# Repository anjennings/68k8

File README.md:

# 68k8

## Specs
+ 68008 CPU
+ 68681 UART
+ 32K EEPROM
+ 2 x 512k SRAM Sockets 
	+ 2nd chip (lower) optional
+ Serial EEPROM 
	+ Remotely Programable
	+ Sizes Vary but 64k-128k Recommended
+ Micro SD Card
	+ I haven't even begun to test this so idk

## TODO List 1/7/21 (preferably in this order)
+ Arduino code for programming SROM
+ Wait for new 68681 chips to arrive
+ Finish UART A drivers
+ Finish Timer drivers
+ Test/Finish SROM Drivers
+ Order higher capacity SROM
+ Order sd card slot
+ Order 32-DIP socket for 2nd RAM slot
+ Write bootloader that boots from SROM
+ Solder SD card
+ Solder 2nd RAM socket
+ Assign traps to UART/SPI functions
+ Fuzix Branch

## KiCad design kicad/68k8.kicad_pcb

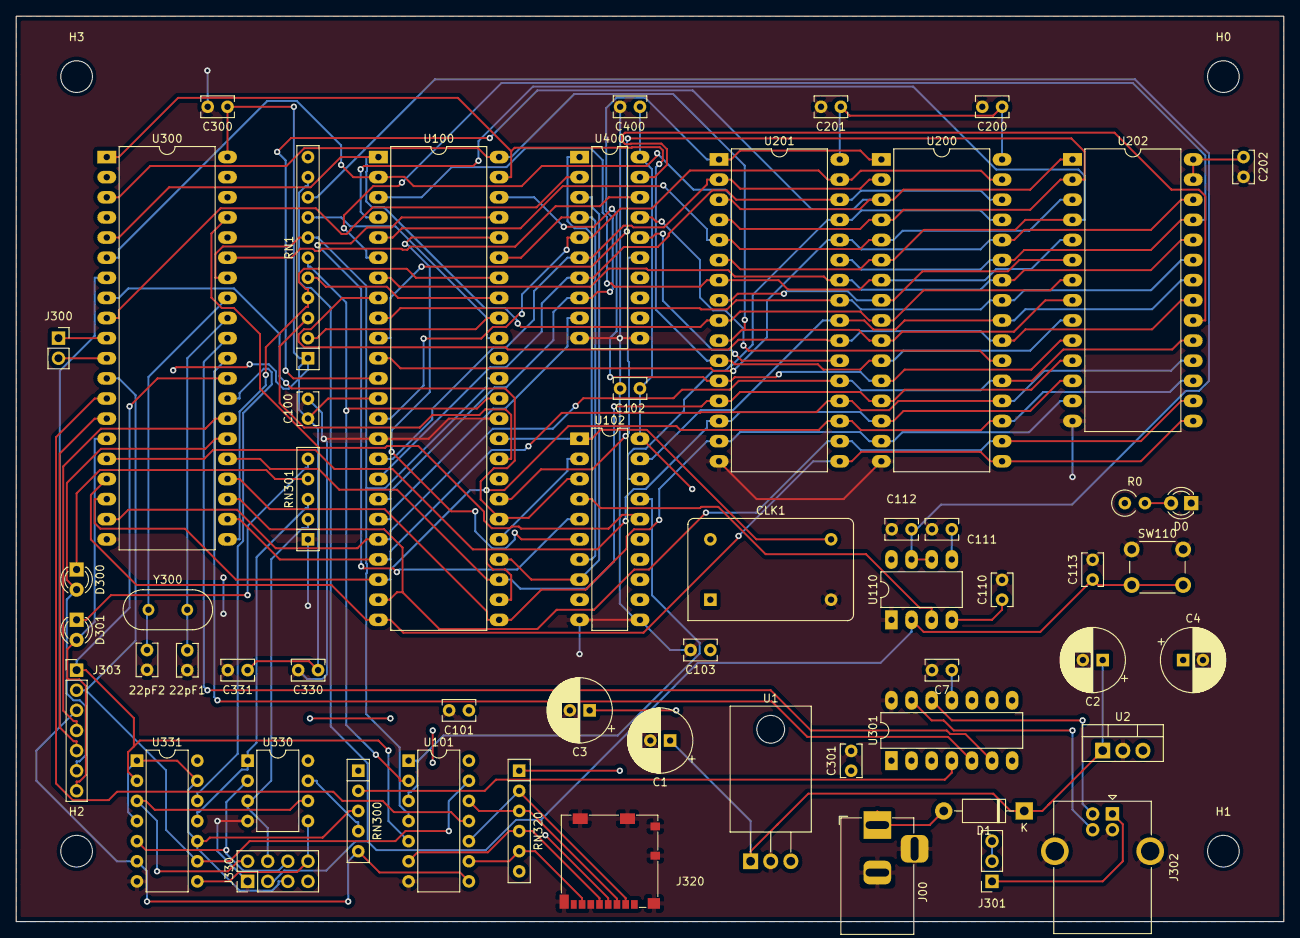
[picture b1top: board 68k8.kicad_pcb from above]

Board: 2 copper layers, 160.0 x 114.3 mm, 60 parts (0 on the bottom side), 96 nets.

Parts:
22pF1: CX1; C_Rect_L4.0mm_W2.5mm_P2.50mm
22pF2: CX2; C_Rect_L4.0mm_W2.5mm_P2.50mm
C1, C4: .1uF; CP_Radial_D8.0mm_P2.50mm
C2: .33uF; CP_Radial_D8.0mm_P2.50mm
C3: 2.2uF; CP_Radial_D8.0mm_P2.50mm
C7, C100, C101, C102, C103, C110, C200, C201, C202, C300, C301, C330, C331, C400: 22pF; C_Rect_L4.0mm_W2.5mm_P2.50mm
C111: 10nF; C_Rect_L4.0mm_W2.5mm_P2.50mm
C112: 10uF; C_Rect_L4.0mm_W2.5mm_P2.50mm
C113: 100nF; C_Rect_L4.0mm_W2.5mm_P2.50mm
CLK1: 10.000 MHz; Oscillator_DIP-14
D0: POW_LED; LED_D3.0mm
D1: 1N4001; D_DO-41_SOD81_P10.16mm_Horizontal
D300, D301: LED; LED_D3.0mm
H0, H1, H2, H3: MountingHole; MountingHole_4mm
J00: Barrel_Jack_Switch; BarrelJack_Horizontal
J300: Conn_01x02_Male; PinSocket_1x02_P2.54mm_Vertical
J301: Conn_01x03_Male; PinSocket_1x03_P2.54mm_Vertical
J302: USB_B; USB_B_OST_USB-B1HSxx_Horizontal
J303: Conn_01x07; PinHeader_1x07_P2.54mm_Vertical
J320: Micro_SD_Card_Det; microSD_HC_Molex_104031-0811
J330: Conn_02x04_Top_Bottom; PinHeader_2x04_P2.54mm_Vertical
R0: 2K; R_Axial_DIN0309_L9.0mm_D3.2mm_P2.54mm_Vertical
RN1: R_Network10; R_Array_SIP11
RN300: 10K; R_Array_SIP5
RN301: 2K; R_Array_SIP5
RN320: 10k; R_Array_SIP6
SW110: SW_Push; SW_PUSH_6mm_H8.5mm
U1: LF33_TO220; TO-220-3_Horizontal_TabDown
U2: L7805; TO-220-3_Vertical
U100: 68008D; DIP-48_W15.24mm_LongPads
U101: 74LS07; DIP-14_W7.62mm
U102, U400: GAL16V8; DIP-20_W7.62mm_LongPads
U110: LM555; DIP-8_W7.62mm_LongPads
U200, U201: AS6C4008-55PCN; DIP-32_W15.24mm_LongPads
U202: 28C256; DIP-28_W15.24mm_LongPads
U300: 68681; DIP-40_W15.24mm_LongPads
U301: MCP2221AxP; DIP-14_W7.62mm_LongPads
U330: 25LCxxx; DIP-8_W7.62mm
U331: 74LS126; DIP-14_W7.62mm
Y300: 3.6864 MHz; Crystal_HC18-U_Vertical

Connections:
555_01: C112.1, RN1.9, U110.6, U110.7
+3V3: C3.1, J320.4, RN320.1, U1.3
+5V: C4.1, C100.1, C101.1, C102.1, C103.1, C110.1, C200.1, C201.1, C202.1, C300.1, C301.1, C330.1, C331.1, C400.1, CLK1.14, J330.7, R0.1, RN1.1, RN300.1, U2.3, U100.13, U101.14, U102.20, U110.4, U110.8, U200.32, U201.32, U202.27, U202.28, U300.40, U301.1, U330.8, U331.14, U400.20
/100_CPU/110_RESET/Reset: U102.4, U110.3
/100_CPU/A0: U100.46, U200.12, U201.12, U202.10
/100_CPU/A1: U100.47, U200.11, U201.11, U202.9, U300.1
/100_CPU/A2: U100.48, U200.10, U201.10, U202.8, U300.3
/100_CPU/A3: U100.1, U200.9, U201.9, U202.7, U300.5
/100_CPU/A4: U100.2, U200.8, U201.8, U202.6, U300.6
/100_CPU/A5: U100.3, U200.7, U201.7, U202.5
/100_CPU/A6: U100.4, U200.6, U201.6, U202.4
/100_CPU/A7: U100.5, U200.5, U201.5, U202.3
/100_CPU/A8: U100.6, U200.27, U201.27, U202.25
/100_CPU/A9: U100.7, U200.26, U201.26, U202.24
/100_CPU/A10: U100.8, U200.23, U201.23, U202.21
/100_CPU/A11: U100.9, U200.25, U201.25, U202.23
/100_CPU/A12: U100.10, U200.4, U201.4, U202.2
/100_CPU/A13: U100.11, U200.28, U201.28, U202.26
/100_CPU/A14: U100.12, U200.3, U201.3, U202.1
/100_CPU/A15: U100.14, U200.31, U201.31, U400.5
/100_CPU/A16: U100.16, U200.2, U201.2, U400.6
/100_CPU/A17: U100.17, U200.30, U201.30, U400.7
/100_CPU/A18: U100.18, U200.1, U201.1, U400.8
/100_CPU/A19: U100.19, U400.9
/100_CPU/D0: U100.27, U200.13, U201.13, U202.11, U300.25
/100_CPU/D1: U100.26, U200.14, U201.14, U202.12, U300.16
/100_CPU/D2: U100.25, U200.15, U201.15, U202.13, U300.24
/100_CPU/D3: U100.24, U200.17, U201.17, U202.15, U300.17
/100_CPU/D4: U100.23, U200.18, U201.18, U202.16, U300.23
/100_CPU/D5: U100.22, U200.19, U201.19, U202.17, U300.18
/100_CPU/D6: U100.21, U200.20, U201.20, U202.18, U300.22
/100_CPU/D7: U100.20, U200.21, U201.21, U202.19, U300.19
AS: U100.28, U102.8, U400.3
AUX_CS1: J303.4, U300.27
AUX_CS2: J303.5, U300.14
AUX_CS3: D300.2, J303.6, U300.26
AUX_CS4: D301.2, J303.7, U300.15
BERR: RN1.2, U100.40
BR: RN1.3, U100.33
CLK: CLK1.8, U100.34, U102.1, U400.1
DART_DTACK: U300.9, U400.2
DART_IRQ: RN1.4, U100.42, U300.21
DART_RX: U300.31, U301.6
DART_TX: U300.30, U301.5
DS: U100.29, U102.2
DTACK: U100.31, U400.15
FC0: U100.45, U102.5
FC1: U100.44, U102.6
FC2: U100.43, U102.7, U400.4
GND: 22pF1.1, 22pF2.1, C1.2, C2.2, C3.2, C4.2, C7.2, C100.2, C101.2, C102.2, C103.2, C110.2, C111.2, C112.2, C113.2, C200.2, C201.2, C202.2, C300.2, C301.2, C330.2, C331.2, C400.2, CLK1.7, D0.1, J00.2, J00.3, J302.4, J302.5, J320.6, J320.9, J320.10, J320.11, J330.1, RN301.1, SW110.1, U1.2, U2.2, U100.15, U100.35, U101.7, U102.10, U102.11, U110.1, U200.16, U201.16, U202.14, U300.20, U301.14, U330.4, U331.7, U400.10, U400.11
HALT: RN1.6, U100.36, U101.2
HRAM_SEL: U200.22, U400.17
INTACK: U102.16, U300.37
IO1_SEL: U300.35, U400.18
IP1: RN1.5, U100.41
LRAM_SEL: U201.22, U400.16
MISO: J303.3, RN300.5, U101.8, U300.7, U331.6
MOSI: J303.2, U101.13, U300.12, U331.9
unnamed: 22pF1.2, U300.32, Y300.1
unnamed: 22pF2.2, U300.33, Y300.2
unnamed: C7.1, U301.11
unnamed: C111.1, U110.5
unnamed: D0.2, R0.2
unnamed: D1.2, J00.1
unnamed: D300.1, RN301.4
unnamed: D301.1, RN301.5
unnamed: J300.1, U300.10
unnamed: J300.2, U300.11
unnamed: J301.1, J302.1
unnamed: J301.2, J301.3
unnamed: J302.2, U301.12
unnamed: J302.3, U301.13
unnamed: J320.2, RN320.2, U101.10
unnamed: J320.3, RN320.3, U101.12
unnamed: J320.5, RN320.4, U101.6
unnamed: J320.7, RN320.5, U101.9
unnamed: U101.1, U101.3, U102.17
PROG_EN: J330.5, RN300.3, U331.1, U331.4, U331.10, U331.13
PROG_MISO: J330.6, U330.2, U331.5
PROG_MOSI: J330.8, U330.5, U331.8
PROG_SCLK: J330.2, U330.6, U331.3
PROG_WP: J330.4, RN301.2, U330.3
READ: U102.19, U200.24, U201.24, U202.22
RESET: RN1.7, U100.37, U101.4, U300.34
RESET_IN: C113.1, J330.3, RN1.10, SW110.2, U110.2
ROM_CS: U300.28, U331.12
ROM_SEL: U202.20, U400.19
RW: U100.30, U102.3, U300.8
SCLK: J303.1, U101.5, U300.29, U331.2
SD_CS: U101.11, U300.13
SER_PD2: RN301.3, U330.1, U331.11
SER_PU2: RN300.4, U330.7
USB_RST: RN300.2, U301.4
VCC: C1.1, C2.1, D1.1, U1.1, U2.1
VPA: RN1.8, U100.39
WRITE: U102.18, U200.29, U201.29

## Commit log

2021-08-01 Init
2021-10-11 updates from a long time ago
2021-10-11 removed full 68 file
2021-10-11 Replaced most logic with EEPLD
2021-11-30 Almost ready to route the PCB fully
2021-11-30 removed rom/ram routes
2021-12-01 moved larger footprints around a bit
2021-12-02 ran autoroute
2021-12-02 redid layout
2021-12-02 key routes placed
2021-12-03 redid power routes
2021-12-04 almost done, almost
2021-12-05 init galdev
2021-12-05 1st attempt at GAL logic
2021-12-05 gerbers have been sent
2021-12-05 created makefile
2021-12-05 added 2nd gal logic
2021-12-08 Generated BOM
2021-12-08 Removed unused files
2021-12-08 removed duplicates
2021-12-08 more unused files
2021-12-08 Squashed commit of the following:
    commit 5bb93159fc2b2eccf3bc7271ff40b3cebe761d34
    Author: Aidan Jennings <anjennings@wisc.edu>
    Date: Wed Dec 8 17:37:30 2021 -0600
    more unused files
    commit 7e13d52fce64914ddbd187ffc850994f54d80316
    Author: Aidan Jennings <anjennings@wisc.edu>
2021-12-11 starting on bios
2021-12-11 added assembly makefile
2021-12-12 switched asmbler to VASM
2021-12-12 Began on DUART drivers
2021-12-12 added more to bios
2021-12-18 updated makefiles and 400 logic
2021-12-18 Exported schematics
2021-12-18 Squashed commit of the following:
    commit eabfd99e5b4e6e7f1b8568df38c8654b5fd99cff
    Author: anjennings <anjennings@wisc.edu>
    Date: Fri Dec 17 18:34:44 2021 -0600
    updated makefiles and 400 logic
    commit 65a40b7e8405619080058027aab4196d90c11d98
    Author: anjennings <anjennings@wisc.edu>
2021-12-18 updated gal logic
2021-12-19 we have blinkenlights!
2021-12-19 Filled in vector table
2021-12-20 split bios up across multiple files
2021-12-20 Updating readmes
2021-12-21 Added arduino code for testing chips
2021-12-21 I'm losing my wits with this uart
2021-12-29 more DUART drivers
2021-12-29 srom and generic spi drivers
2021-12-29 changes to arduino code
2022-01-04 added macros for stack operations
2022-01-06 More functions for SROM
2022-09-04 added arduino scope code
2022-09-04 bad GAL logic
2022-09-04 Old BIOS dev and GAL changes (#3)
    * starting on bios
    * added assembly makefile
    * switched asmbler to VASM
    * Began on DUART drivers
    * added more to bios
    * Exported schematics
